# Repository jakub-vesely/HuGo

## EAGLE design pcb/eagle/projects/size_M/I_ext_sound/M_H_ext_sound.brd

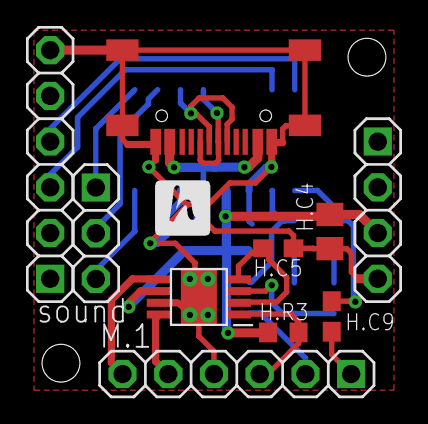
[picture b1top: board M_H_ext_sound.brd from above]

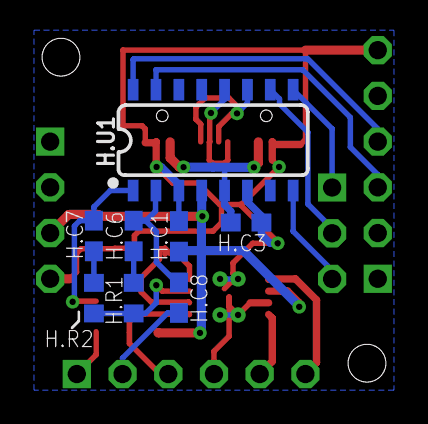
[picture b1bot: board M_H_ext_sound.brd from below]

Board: 2 copper layers, 18 parts (8 on the bottom side), 21 nets.

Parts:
H.C1, H.C5, H.C6, H.C7, H.C8, H.C9: 100n; C0603
H.C3: 1u; C0603
H.C4: 10u (22u); C0805
H.J1, H.J2: 1X06
H.R1, H.R2: 100k; R0603
H.R3: 10k; R0603
H.U1: WT2003S; SO16
H.U2: TPA6211; MSOP-POWERPAD-8
H.USB: USB-C
JP1: 1X03
JP2: 1X04

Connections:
GND: H.C1.2, H.C3.2, H.C4.1, H.C5.1, H.J1.4, H.J2.6, H.U1.3, H.U1.6, H.U2.7, H.U2.9, H.U2.P$10, H.U2.P$11, H.U2.P$12, H.U2.P$13, H.USB.A1B12, H.USB.B1A12, H.USB.SH1, H.USB.SH2, H.USB.SH3, H.USB.SH4, JP2.4
unnamed: H.C8.2, H.J1.2
unnamed: H.C9.2, H.J1.1
unnamed: H.J1.5, H.U2.8
unnamed: H.J2.3, H.U1.15
unnamed: H.J2.4, H.U1.16
unnamed: H.J1.6, H.U2.5
unnamed: H.J1.3, H.R3.1, H.U2.1
unnamed: H.U1.10, JP1.2
unnamed: H.U1.12, H.USB.A6, H.USB.B6
unnamed: H.U1.11, H.USB.A7, H.USB.B7
unnamed: H.C3.1, H.U1.5, H.USB.A4B9, H.USB.B4A9
unnamed: H.C6.1, H.C8.1, H.U1.2
unnamed: H.C7.1, H.C9.1, H.U1.1
unnamed: H.R1.2, H.R2.2, H.U2.3
unnamed: H.C5.2, H.U2.2, H.U2.4
unnamed: H.U1.9, JP1.1
unnamed: H.C6.2, H.R1.1
unnamed: H.C7.2, H.R2.1
unnamed: H.U1.8, JP1.3
VCC: H.C1.1, H.C4.2, H.R3.2, H.U1.4, H.U2.6, JP2.3

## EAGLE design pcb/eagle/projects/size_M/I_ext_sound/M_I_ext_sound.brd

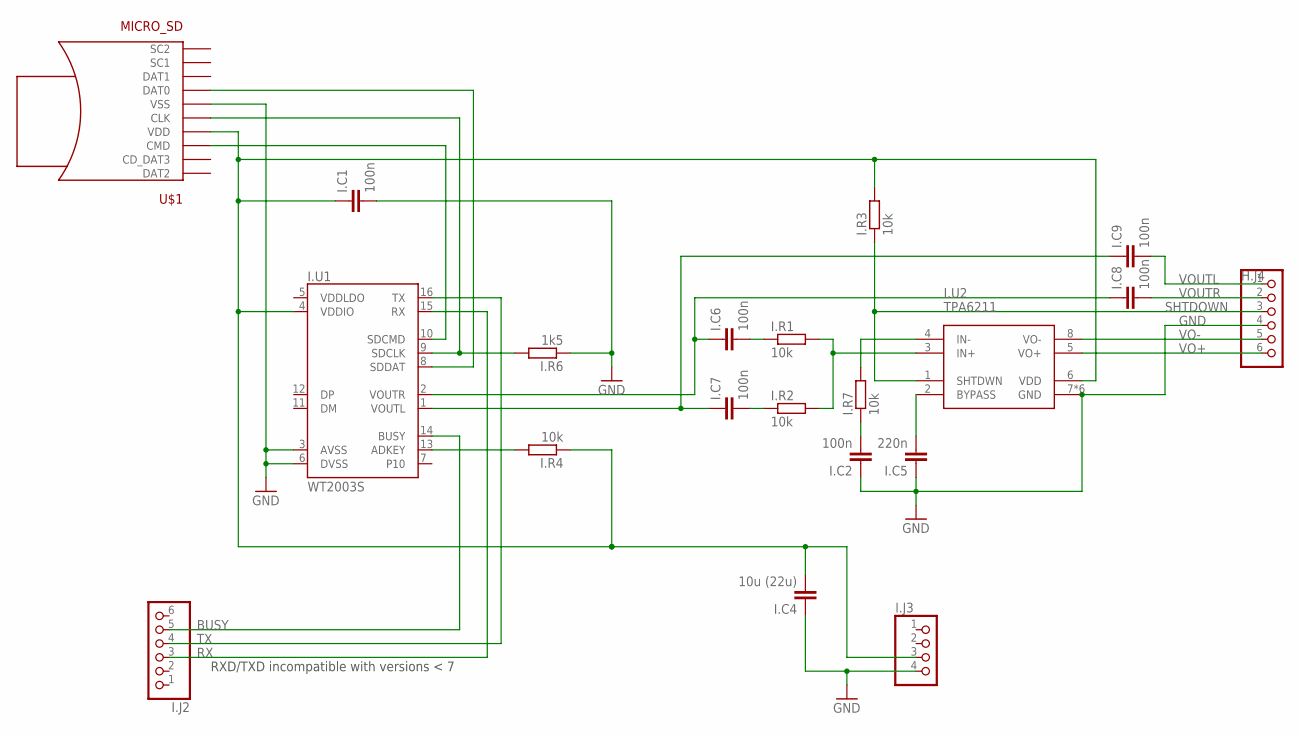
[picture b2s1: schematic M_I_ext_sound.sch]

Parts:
H.J4: PINHD-1X6; 1X06
I.C1, I.C2, I.C6, I.C7, I.C8, I.C9: 100n; C0603
I.C4: 10u (22u); C0805
I.C5: 220n; C0603
I.J2: PINHD-1X6; 1X06
I.J3: PINHD-1X4; 1X04
I.R1, I.R2, I.R3, I.R4, I.R7: 10k; R0603
I.R6: 1k5; R0603
I.U1: WT2003S; SO16
I.U2: TPA6211; MSOP-POWERPAD-8
U$1: MICRO_SD; MOCRO_SD

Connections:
BUSY: I.J2.5, I.U1.14 (BUSY)
GND: H.J4.4, I.C1.2, I.C2.1, I.C4.1, I.C5.1, I.J3.4, I.R6.1, I.U1.3 (AVSS), I.U1.6 (DVSS), I.U2.7 (GND), I.U2.9 (GND), I.U2.P$10 (GND), I.U2.P$11 (GND), I.U2.P$12 (GND), I.U2.P$13 (GND), U$1.6 (VSS), U$1.G1 (VSS), U$1.G2 (VSS), U$1.G3 (VSS), U$1.G4 (VSS)
unnamed: I.R4.2, I.U1.13 (ADKEY)
unnamed: I.R7.2, I.U2.4 (IN-)
unnamed: I.C2.2, I.R7.1
unnamed: I.C6.1, I.C8.1, I.U1.2 (VOUTR)
unnamed: I.C7.1, I.C9.1, I.U1.1 (VOUTL)
unnamed: I.R1.2, I.R2.2, I.U2.3 (IN+)
unnamed: I.C5.2, I.U2.2 (BYPASS)
unnamed: I.C6.2, I.R1.1
unnamed: I.C7.2, I.R2.1
RX: I.J2.3, I.U1.15 (RX)
SDCLK: I.R6.2, I.U1.9 (SDCLK), U$1.5 (CLK)
SDCMD: I.U1.10 (SDCMD), U$1.3 (CMD)
SDDAT: I.U1.8 (SDDAT), U$1.7 (DAT0)
SHTDOWN: H.J4.3, I.R3.1, I.U2.1 (SHTDWN)
TX: I.J2.4, I.U1.16 (TX)
VCC: I.C1.1, I.C4.2, I.J3.3, I.R3.2, I.R4.1, I.U1.4 (VDDIO), I.U2.6 (VDD), U$1.4 (VDD)
VO+: H.J4.6, I.U2.5 (VO+)
VO-: H.J4.5, I.U2.8 (VO-)
VOUTL: H.J4.1, I.C9.2
VOUTR: H.J4.2, I.C8.2

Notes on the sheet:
RXD/TXD incompatible with versions < 7

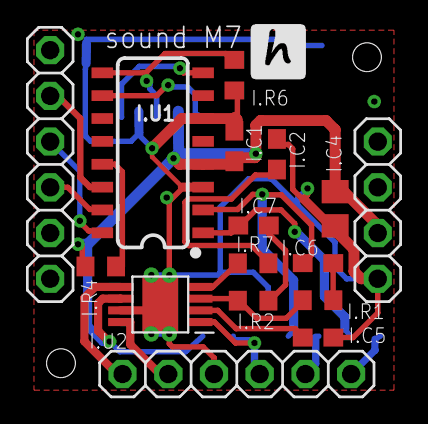
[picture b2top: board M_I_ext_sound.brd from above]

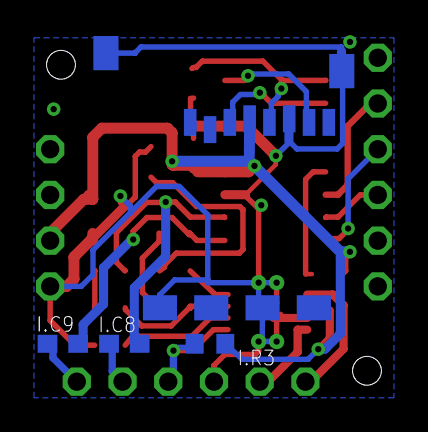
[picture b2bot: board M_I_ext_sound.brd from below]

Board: 2 copper layers, 20 parts (4 on the bottom side), 22 nets.

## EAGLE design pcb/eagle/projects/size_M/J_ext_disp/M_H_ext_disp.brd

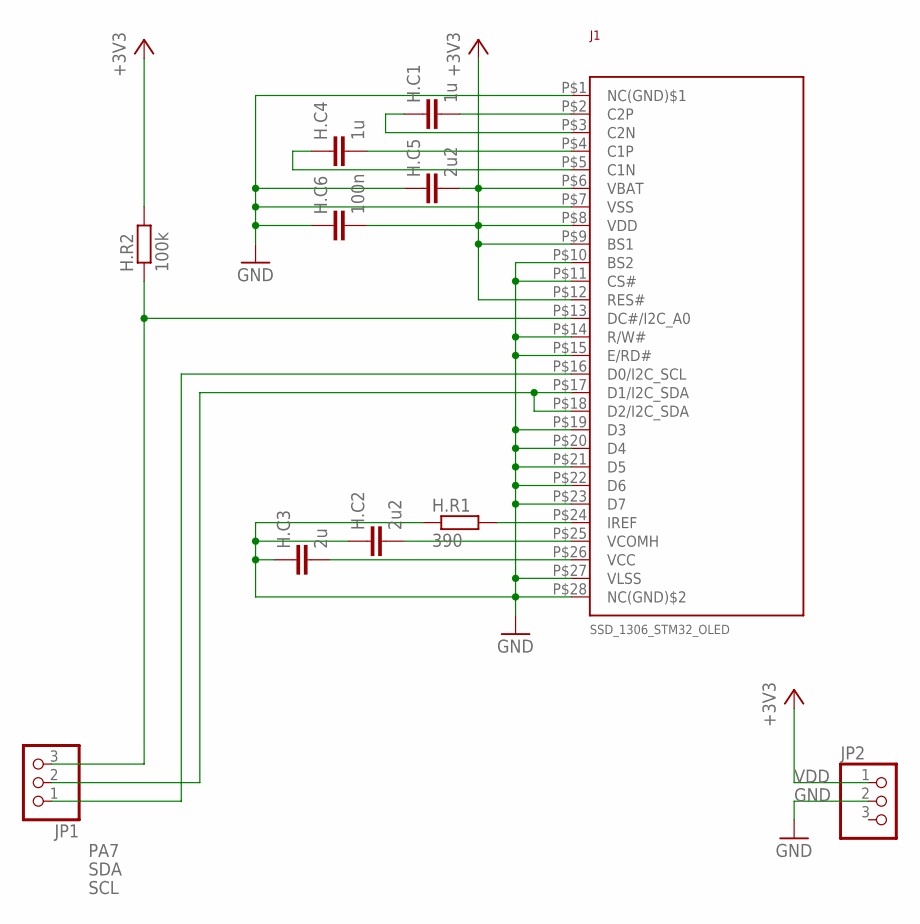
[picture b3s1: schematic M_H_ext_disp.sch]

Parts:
H.C1, H.C4: 1u; C0603
H.C2, H.C5: 2u2; C0603
H.C3: 2u; C0603
H.C6: 100n; C0603
H.R1: 390; R0603
H.R2: 100k; R0603
J1: SSD_1306_STM32_OLED
JP1, JP2: PINHD-1X3; 1X03

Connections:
GND: H.C2.1, H.C3.1, H.C5.1, H.C6.1, H.R1.1, J1.P$1 (NC(GND)$1), J1.P$7 (VSS), J1.P$10 (BS2), J1.P$11 (CS#), J1.P$14 (R/W#), J1.P$15 (E/RD#), J1.P$19 (D3), J1.P$20 (D4), J1.P$21 (D5), J1.P$22 (D6), J1.P$23 (D7), J1.P$27 (VLSS), J1.P$28 (NC(GND)$2), JP2.2
unnamed: H.R1.2, J1.P$24 (IREF)
unnamed: H.C3.2, J1.P$26 (VCC)
unnamed: H.C2.2, J1.P$25 (VCOMH)
unnamed: H.C1.2, J1.P$2 (C2P)
unnamed: H.C1.1, J1.P$3 (C2N)
unnamed: H.C4.2, J1.P$4 (C1P)
unnamed: H.C4.1, J1.P$5 (C1N)
PA7: H.R2.1, J1.P$13 (DC#/I2C_A0), JP1.3
SCL: J1.P$16 (D0/I2C_SCL), JP1.1
SDA: J1.P$17 (D1/I2C_SDA), J1.P$18 (D2/I2C_SDA), JP1.2
VDD: H.C5.2, H.C6.2, H.R2.2, J1.P$6 (VBAT), J1.P$8 (VDD), J1.P$9 (BS1), J1.P$12 (RES#), JP2.1

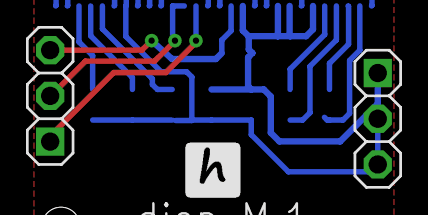
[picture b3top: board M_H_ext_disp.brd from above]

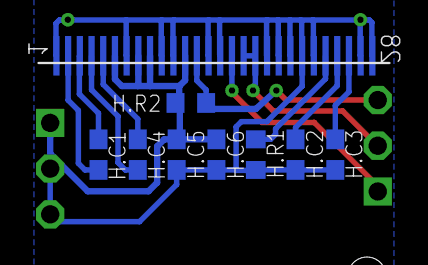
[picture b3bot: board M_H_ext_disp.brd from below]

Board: 2 copper layers, 11 parts (8 on the bottom side), 12 nets.

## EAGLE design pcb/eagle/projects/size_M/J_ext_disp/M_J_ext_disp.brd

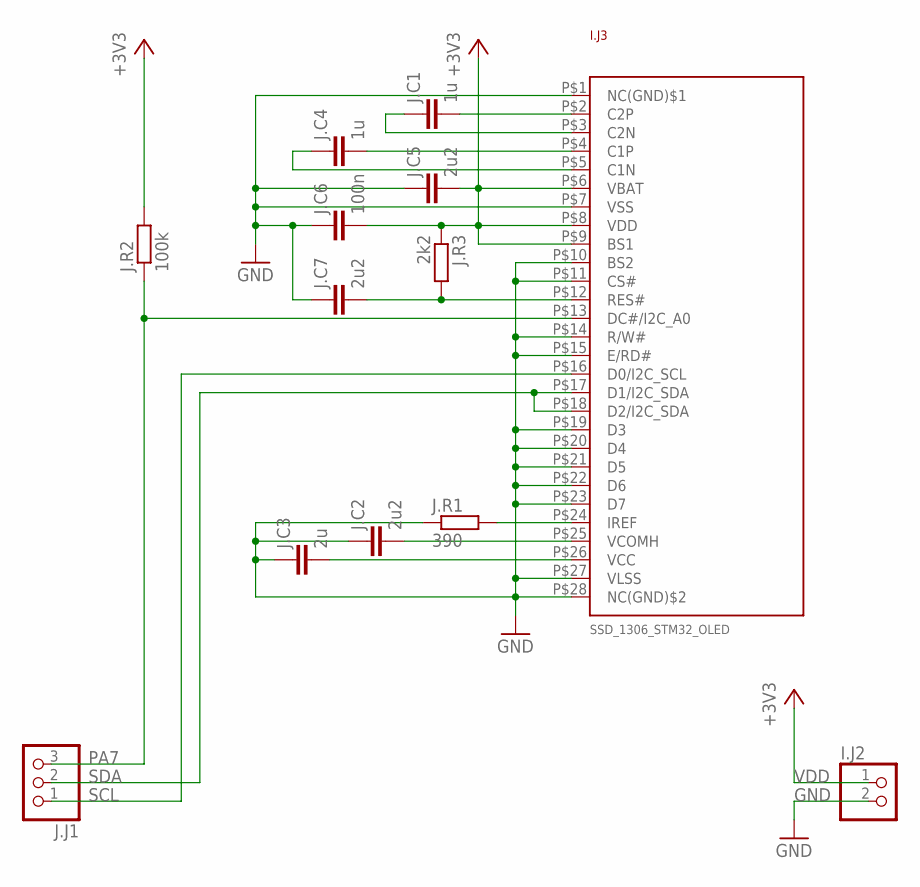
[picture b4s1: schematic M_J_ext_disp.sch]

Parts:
I.J2: PINHD-1X2; 1X02
I.J3: SSD_1306_STM32_OLED
J.C1, J.C4: 1u; C0603
J.C2, J.C5, J.C7: 2u2; C0603
J.C3: 2u; C0603
J.C6: 100n; C0603
J.J1: PINHD-1X3; 1X03
J.R1: 390; R0603
J.R2: 100k; R0603
J.R3: 2k2; R0603

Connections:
GND: I.J2.2, I.J3.P$1 (NC(GND)$1), I.J3.P$7 (VSS), I.J3.P$10 (BS2), I.J3.P$11 (CS#), I.J3.P$14 (R/W#), I.J3.P$15 (E/RD#), I.J3.P$19 (D3), I.J3.P$20 (D4), I.J3.P$21 (D5), I.J3.P$22 (D6), I.J3.P$23 (D7), I.J3.P$27 (VLSS), I.J3.P$28 (NC(GND)$2), J.C2.1, J.C3.1, J.C5.1, J.C6.1, J.C7.1, J.R1.1
unnamed: I.J3.P$24 (IREF), J.R1.2
unnamed: I.J3.P$12 (RES#), J.C7.2, J.R3.2
unnamed: I.J3.P$26 (VCC), J.C3.2
unnamed: I.J3.P$25 (VCOMH), J.C2.2
unnamed: I.J3.P$2 (C2P), J.C1.2
unnamed: I.J3.P$3 (C2N), J.C1.1
unnamed: I.J3.P$4 (C1P), J.C4.2
unnamed: I.J3.P$5 (C1N), J.C4.1
PA7: I.J3.P$13 (DC#/I2C_A0), J.J1.3, J.R2.1
SCL: I.J3.P$16 (D0/I2C_SCL), J.J1.1
SDA: I.J3.P$17 (D1/I2C_SDA), I.J3.P$18 (D2/I2C_SDA), J.J1.2
VDD: I.J2.1, I.J3.P$6 (VBAT), I.J3.P$8 (VDD), I.J3.P$9 (BS1), J.C5.2, J.C6.2, J.R2.2, J.R3.1

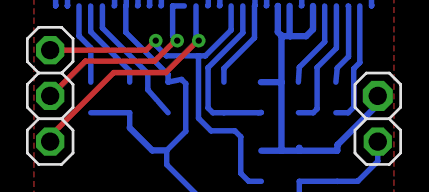
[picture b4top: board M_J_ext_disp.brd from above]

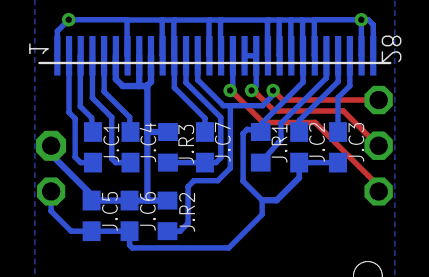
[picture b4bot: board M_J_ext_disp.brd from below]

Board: 2 copper layers, 13 parts (10 on the bottom side), 13 nets.

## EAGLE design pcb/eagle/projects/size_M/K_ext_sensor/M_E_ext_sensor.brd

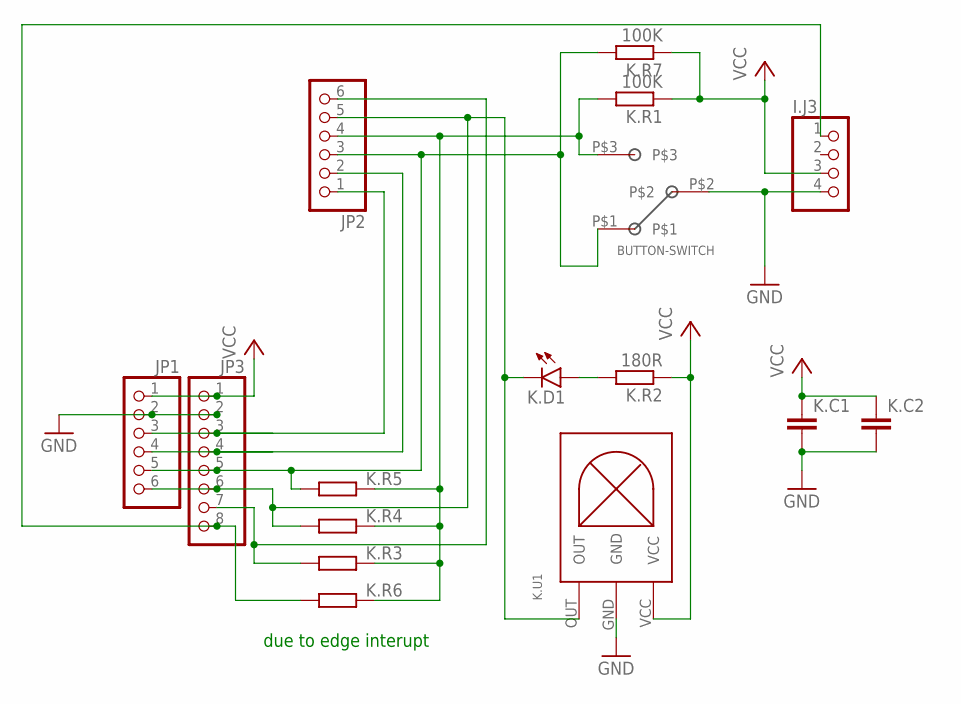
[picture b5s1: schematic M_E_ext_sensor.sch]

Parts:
I.J3: PINHD-1X4; 1X04
JP1, JP2: PINHD-1X6; 1X06
JP3: PINHD-1X8; 1X08
K.C1, K.C2: C-EUC0603; C0603
K.D1: LEDCHIP-LED0603; CHIP-LED0603
K.R1, K.R7: 100K; R0603
K.R2: 180R; R0603
K.R3, K.R4, K.R5, K.R6: 0R; R0603
K.U1: VS1838B; IR_RECEIVER
U$2: BUTTON-SWITCH

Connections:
GND: I.J3.4, JP1.2, JP3.2, K.C1.2, K.C2.2, K.U1.GND, U$2.P$2
unnamed: JP2.4, K.R1.2, K.R3.1, K.R4.1, K.R5.1, K.R6.1, U$2.P$3
unnamed: JP1.5, JP2.3, JP3.5, K.R5.2, K.R7.2, U$2.P$1
unnamed: JP1.4, JP2.2, JP3.4
unnamed: JP1.3, JP2.1, JP3.3
unnamed: K.D1.A1 (A), K.R2.2
unnamed: JP2.6, JP3.7, K.R3.2
unnamed: I.J3.1, JP3.8, K.R6.2
unnamed: JP1.6, JP2.5, JP3.6, K.D1.C1 (C), K.R4.2, K.U1.OUT
VCC: I.J3.3, JP1.1, JP3.1, K.C1.1, K.C2.1, K.R1.1, K.R2.1, K.R7.1, K.U1.VCC

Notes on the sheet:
due to edge interupt

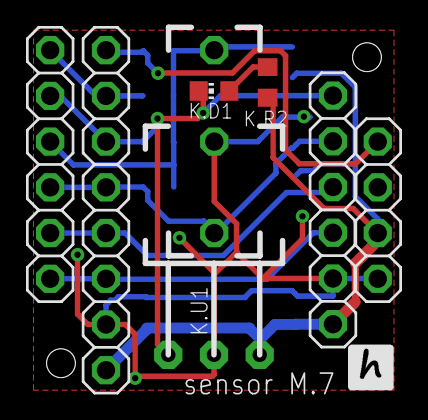
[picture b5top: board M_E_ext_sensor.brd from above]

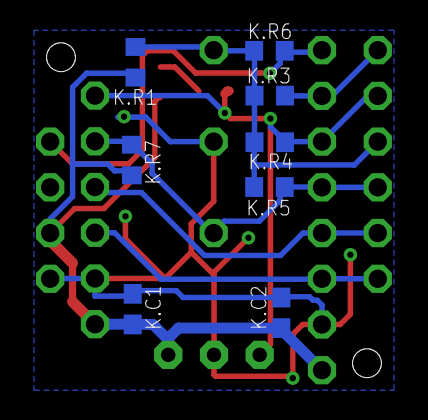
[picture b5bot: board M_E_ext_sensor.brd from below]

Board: 2 copper layers, 16 parts (8 on the bottom side), 10 nets.

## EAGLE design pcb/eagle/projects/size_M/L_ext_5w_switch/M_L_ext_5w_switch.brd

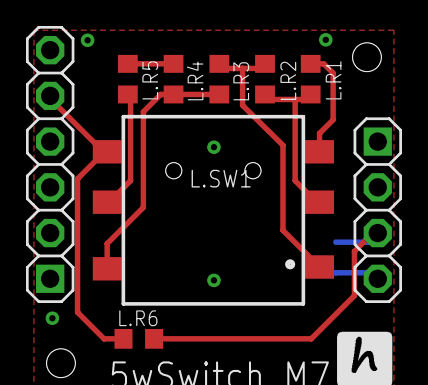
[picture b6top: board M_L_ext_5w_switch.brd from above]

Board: 2 copper layers, 10 parts (1 on the bottom side), 8 nets.

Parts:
G.J1: 1X06
G.J2: 1X04
L.C1: 100n; C0603
L.R1, L.R2: 1k; R0603
L.R3, L.R4, L.R5, L.R6: 2k2; R0603
L.SW1: 5_WAY_SWITCH

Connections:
GND: G.J2.4, L.C1.1, L.R1.2, L.SW1.4
unnamed: L.R4.1, L.R5.1
unnamed: L.R1.1, L.R2.2, L.SW1.5
unnamed: L.R2.1, L.R3.2, L.SW1.6
unnamed: L.R3.1, L.R4.2, L.SW1.3
unnamed: G.J1.5, L.R6.1, L.SW1.1
unnamed: L.R5.2, L.SW1.2
VCC: G.J2.3, L.C1.2, L.R6.2
